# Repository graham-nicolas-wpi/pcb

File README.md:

# Modular NeoPixel Smart Clock

This repository contains the full clock project for a custom four-digit NeoPixel display board and its long-term two-MCU software stack.

## Permanent Hardware Direction

The custom PCB stays physically unchanged.

- Arduino Leonardo remains on the board as the permanent renderer and board-native hardware controller
- ESP32-WROOM-32E is the external high-level host platform
- ESP32 talks to Leonardo over exposed header pins only
- ESP32 does not directly drive `LED_DIN`
- no PCB redesign and no soldering to hidden custom-board traces are part of the main plan

Preferred UART link:

- ESP32 `GPIO17 TX` -> Leonardo `D0 / RX`
- Leonardo `D1 / TX` -> ESP32 `GPIO16 RX` through a divider or level shifter
- common `GND`

## Repo Layout

- `hardware/pcb/` - KiCad sources, fabrication outputs, schematic exports
- `firmware/arduino/clock_firmware/` - Leonardo renderer runtime using the `ClockRender/1` protocol
- `firmware/arduino/clock_calibration_firmware/` - Leonardo calibration and map-writing firmware using `ClockCal/1`
- `firmware/platformio/esp32_clock/` - ESP32 host platform with web UI, storage, time/network logic, and renderer link control
- `softwear/clockWinder_gui/` - desktop serial tools for Leonardo runtime and calibration workflows
- `docs/leonardo-renderer-esp32-host.md` - canonical coprocessor architecture and serial/render contract

## MCU Responsibilities

### Leonardo

The Leonardo is the stable board appliance:

- renders digits, colon, and decimal to the onboard NeoPixels
- keeps LED mapping and physical calibration authoritative on-board
- reads board buttons and RTC
- exposes a compact serial contract
- supports local fallback clock/timer/stopwatch behavior when no host is attached

### ESP32

The ESP32 is the product brain:

- owns presets, faces, widgets, schedules, and runtime config
- owns NTP, Wi-Fi, storage, browser UI, and future integrations
- compiles rich features into stable renderer commands or `FRAME24` payloads
- treats the Leonardo as a renderer coprocessor instead of replacing it

## Recommended Reading

- Firmware overview: [firmware/README.md](firmware/README.md)
- Leonardo/ESP32 contract: [docs/leonardo-renderer-esp32-host.md](docs/leonardo-renderer-esp32-host.md)
- ESP32 host overview: [firmware/platformio/esp32_clock/README.md](firmware/platformio/esp32_clock/README.md)
- ESP32 host architecture: [firmware/platformio/esp32_clock/ARCHITECTURE.md](firmware/platformio/esp32_clock/ARCHITECTURE.md)
- Desktop GUI notes: [softwear/clockWinder_gui/README.md](softwear/clockWinder_gui/README.md)

## Recommended Workflow

### Bring up the board renderer

1. Flash `firmware/arduino/clock_firmware/` to the Leonardo for normal operation
2. Flash `firmware/arduino/clock_calibration_firmware/` only when you need to remap LEDs
3. Use the desktop GUI for direct Leonardo control or calibration

### Build the long-term product platform

1. Work in `firmware/platformio/esp32_clock/`
2. Connect the ESP32 to the Leonardo over the header UART link
3. Add new features on the ESP32 and emit `ClockRender/1` commands or `FRAME24` frames

## Project Status

- The Leonardo runtime is now being stabilized as a durable renderer/runtime coprocessor.
- The ESP32 project is the long-term expansion surface for nearly all new features.
- The calibration workflow remains Leonardo-owned so physical board mapping stays tied to the actual renderer MCU.

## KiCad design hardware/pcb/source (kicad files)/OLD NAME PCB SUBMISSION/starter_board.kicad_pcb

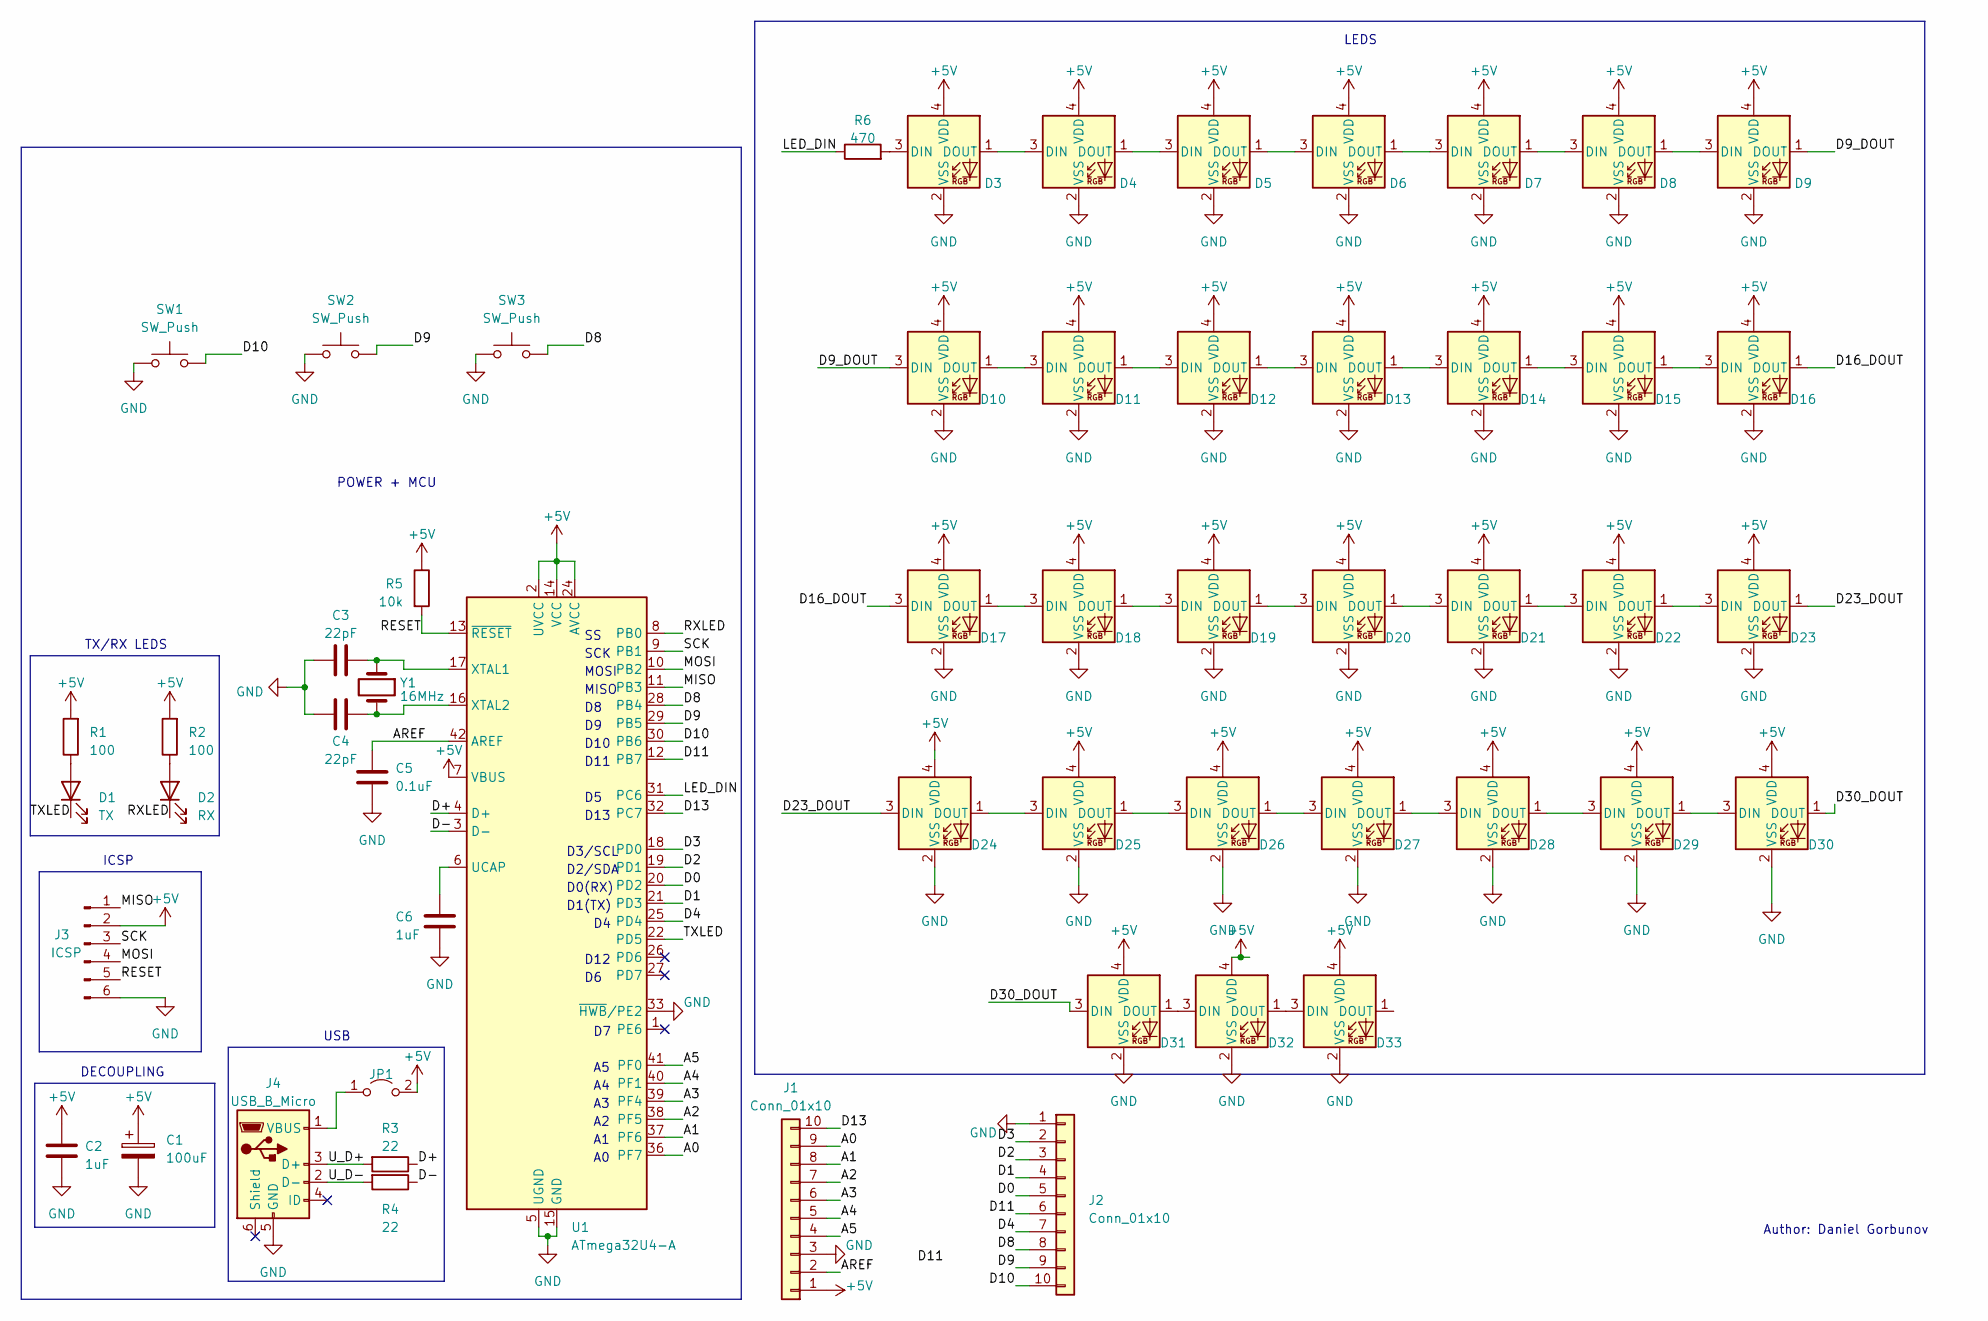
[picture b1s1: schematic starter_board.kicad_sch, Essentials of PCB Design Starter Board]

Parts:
C1: 100uF; CP_Elec_5x5.3
C2, C6: 1uF; C_0805_2012Metric_Pad1.18x1.45mm_HandSolder
C3, C4: 22pF; C_0805_2012Metric_Pad1.18x1.45mm_HandSolder
C5: 0.1uF; C_0805_2012Metric_Pad1.18x1.45mm_HandSolder
D1: TX; LED_0805_2012Metric_Pad1.15x1.40mm_HandSolder
D2: RX; LED_0805_2012Metric_Pad1.15x1.40mm_HandSolder
D3, D4, D5, D6, D7, D8, D9, D10, D11, D12, D13, D14, D15, D16, D17, D18, D19, D20, D21, D22, D23, D24, D25, D26, D27, D28, D29, D30, D31, D32, D33: SK6812MINI; LED_SK6812MINI_PLCC4_3.5x3.5mm_P1.75mm
J1, J2: Conn_01x10; PinHeader_1x10_P2.54mm_Vertical
J3: ICSP; PinHeader_2x03_P2.54mm_Vertical
J4: USB_B_Micro; USB_Micro-B_GCT_USB3076-30-A
JP1: Jumper_2_Open; SolderJumper-2_P1.3mm_Open_TrianglePad1.0x1.5mm
R1, R2: 100; R_0805_2012Metric_Pad1.20x1.40mm_HandSolder
R3, R4: 22; R_0805_2012Metric_Pad1.20x1.40mm_HandSolder
R5: 10k; R_0805_2012Metric_Pad1.20x1.40mm_HandSolder
R6: 470; R_0805_2012Metric_Pad1.20x1.40mm_HandSolder
SW1, SW2, SW3: SW_Push; SW_SPST_PTS647_Sx50
U1: ATmega32U4-A; TQFP-44_10x10mm_P0.8mm
Y1: 16MHz; Crystal_SMD_5032-2Pin_5.0x3.2mm

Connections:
+5V: C1.1, C2.1, D3.4 (VDD), D4.4 (VDD), D5.4 (VDD), D6.4 (VDD), D7.4 (VDD), D8.4 (VDD), D9.4 (VDD), D10.4 (VDD), D11.4 (VDD), D12.4 (VDD), D13.4 (VDD), D14.4 (VDD), D15.4 (VDD), D16.4 (VDD), D17.4 (VDD), D18.4 (VDD), D19.4 (VDD), D20.4 (VDD), D21.4 (VDD), D22.4 (VDD), D23.4 (VDD), D24.4 (VDD), D25.4 (VDD), D26.4 (VDD), D27.4 (VDD), D28.4 (VDD), D29.4 (VDD), D30.4 (VDD), D31.4 (VDD), D32.4 (VDD), D33.4 (VDD), J1.1, J3.2, JP1.2 (B), R1.2, R2.2, R5.1, U1.2 (UVCC), U1.7 (VBUS), U1.14 (VCC), U1.24 (AVCC), U1.34 (VCC), U1.44 (AVCC)
/A0: J1.9, U1.36 (PF7)
/A1: J1.8, U1.37 (PF6)
/A2: J1.7, U1.38 (PF5)
/A3: J1.6, U1.39 (PF4)
/A4: J1.5, U1.40 (PF1)
/A5: J1.4, U1.41 (PF0)
/AREF: C5.1, J1.2, U1.42 (AREF)
/D0: J2.5, U1.20 (PD2)
/D1: J2.4, U1.21 (PD3)
/D2: J2.3, U1.19 (PD1)
/D3: J2.2, U1.18 (PD0)
/D4: J2.7, U1.25 (PD4)
/D8: J2.8, SW3.2, U1.28 (PB4)
/D9: J2.9, SW2.2, U1.29 (PB5)
/D9_DOUT: D9.1 (DOUT), D10.3 (DIN)
/D10: J2.10, SW1.2, U1.30 (PB6)
/D11: J2.6, U1.12 (PB7)
/D13: J1.10, U1.32 (PC7)
/D16_DOUT: D16.1 (DOUT), D17.3 (DIN)
/D23_DOUT: D23.1 (DOUT), D24.3 (DIN)
/D30_DOUT: D30.1 (DOUT), D31.3 (DIN)
/D+: R3.1, U1.4 (D+)
/D-: R4.1, U1.3 (D-)
/LED_DIN: R6.1, U1.31 (PC6)
/MISO: J3.1, U1.11 (PB3)
/MOSI: J3.4, U1.10 (PB2)
/RESET: J3.5, R5.2, U1.13 (~RESET)
/RXLED: D2.1 (K), U1.8 (PB0)
/SCK: J3.3, U1.9 (PB1)
/TXLED: D1.1 (K), U1.22 (PD5)
/U_D+: J4.3 (D+), R3.2
/U_D-: J4.2 (D-), R4.2
GND: C1.2, C2.2, C3.2, C4.2, C5.2, C6.2, D3.2 (VSS), D4.2 (VSS), D5.2 (VSS), D6.2 (VSS), D7.2 (VSS), D8.2 (VSS), D9.2 (VSS), D10.2 (VSS), D11.2 (VSS), D12.2 (VSS), D13.2 (VSS), D14.2 (VSS), D15.2 (VSS), D16.2 (VSS), D17.2 (VSS), D18.2 (VSS), D19.2 (VSS), D20.2 (VSS), D21.2 (VSS), D22.2 (VSS), D23.2 (VSS), D24.2 (VSS), D25.2 (VSS), D26.2 (VSS), D27.2 (VSS), D28.2 (VSS), D29.2 (VSS), D30.2 (VSS), D31.2 (VSS), D32.2 (VSS), D33.2 (VSS), J1.3, J2.1, J3.6, J4.5 (GND), SW1.1, SW2.1, SW3.1, U1.5 (UGND), U1.15 (GND), U1.23 (GND), U1.33 (~HWB/PE2), U1.35 (GND), U1.43 (GND)
unnamed: D1.2 (A), R1.1
unnamed: D2.2 (A), R2.1
unnamed: D3.3 (DIN), R6.2
unnamed: D3.1 (DOUT), D4.3 (DIN)
unnamed: D4.1 (DOUT), D5.3 (DIN)
unnamed: D5.1 (DOUT), D6.3 (DIN)
unnamed: D6.1 (DOUT), D7.3 (DIN)
unnamed: D7.1 (DOUT), D8.3 (DIN)
unnamed: D8.1 (DOUT), D9.3 (DIN)
unnamed: D10.1 (DOUT), D11.3 (DIN)
unnamed: D11.1 (DOUT), D12.3 (DIN)
unnamed: D12.1 (DOUT), D13.3 (DIN)
unnamed: D13.1 (DOUT), D14.3 (DIN)
unnamed: D14.1 (DOUT), D15.3 (DIN)
unnamed: D15.1 (DOUT), D16.3 (DIN)
unnamed: D17.1 (DOUT), D18.3 (DIN)
unnamed: D18.1 (DOUT), D19.3 (DIN)
unnamed: D19.1 (DOUT), D20.3 (DIN)
unnamed: D20.1 (DOUT), D21.3 (DIN)
unnamed: D21.1 (DOUT), D22.3 (DIN)
unnamed: D22.1 (DOUT), D23.3 (DIN)
unnamed: D24.1 (DOUT), D25.3 (DIN)
unnamed: D25.1 (DOUT), D26.3 (DIN)
unnamed: D26.1 (DOUT), D27.3 (DIN)
unnamed: D27.1 (DOUT), D28.3 (DIN)
unnamed: D28.1 (DOUT), D29.3 (DIN)
unnamed: D29.1 (DOUT), D30.3 (DIN)
unnamed: D31.1 (DOUT), D32.3 (DIN)
unnamed: D32.1 (DOUT), D33.3 (DIN)
unnamed: J4.1 (VBUS), JP1.1 (A)
unnamed: C6.1, U1.6 (UCAP)
unnamed: C3.1, U1.17 (XTAL1), Y1.1
unnamed: C4.1, U1.16 (XTAL2), Y1.2

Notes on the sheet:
MOSI
D2/SDA
LEDS
D11
D3/SCL
USB
DECOUPLING
D1(TX)
D13
Author: Daniel Gorbunov
MISO
D10
POWER + MCU
TX/RX LEDS
ICSP
SCK
D12
D0(RX)

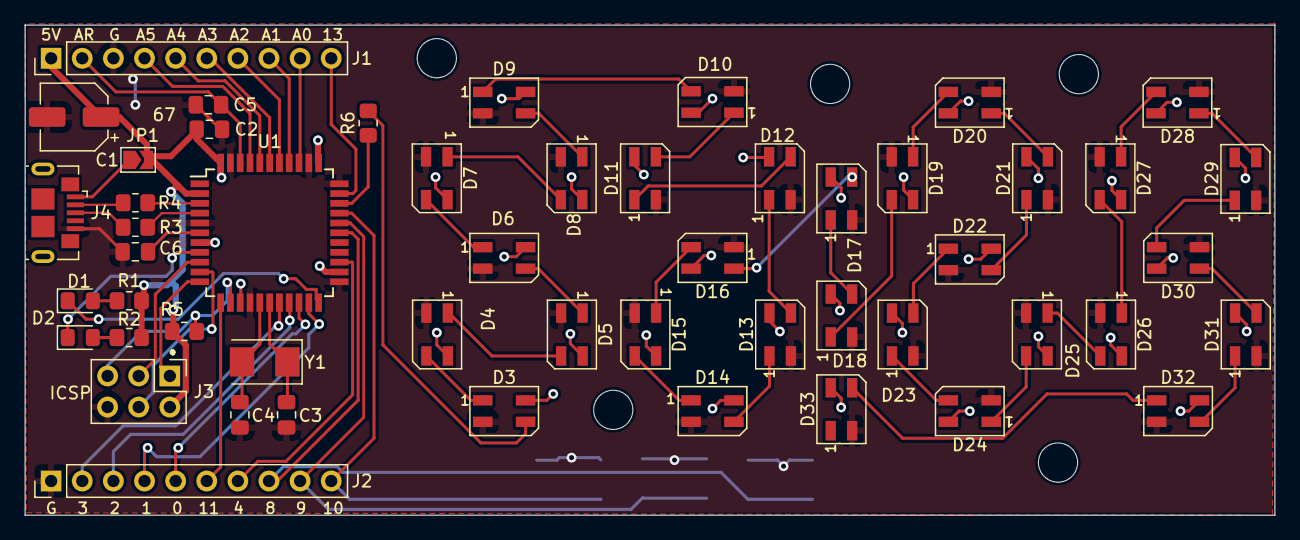
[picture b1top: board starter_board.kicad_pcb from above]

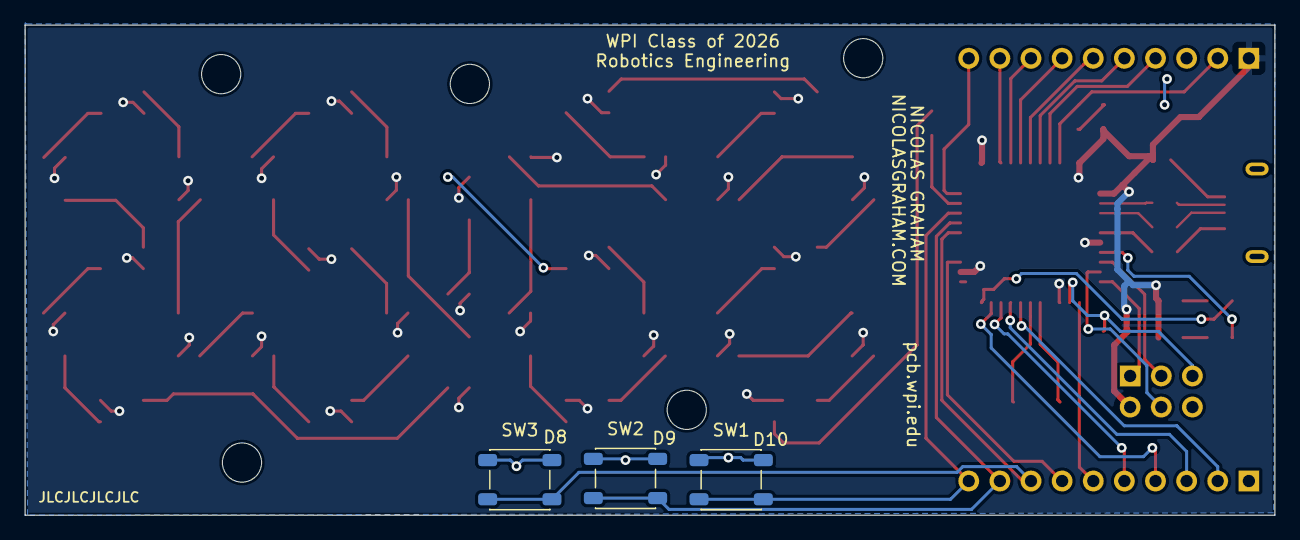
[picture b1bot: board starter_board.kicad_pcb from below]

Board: 2 copper layers, 102.0 x 40.0 mm, 55 parts (3 on the bottom side), 67 nets.

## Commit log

2026-04-13 Archived WPI pcb starter repo
2026-04-13 restructuring
2026-04-14 v1 ig
    -timer
    - clock
    -stopwatch
    -gui
    everything ig lol
    commiting 67 files to main...
2026-04-14 seperation of calibration tool and customization
2026-04-14 transfer to esp32 overhaul
2026-04-14 cleanup
2026-04-14 Changed for external esp32 dual mcu architechture
    innitial esp32 layout was flayed, assumed bypassing onboard chip,
    in reality this is not practical and needed esp32 to drive and leonardo to render the stuff.
2026-05-20 working perf (maybe note tweaks coming soon)
2026-05-22 final changes - full song
